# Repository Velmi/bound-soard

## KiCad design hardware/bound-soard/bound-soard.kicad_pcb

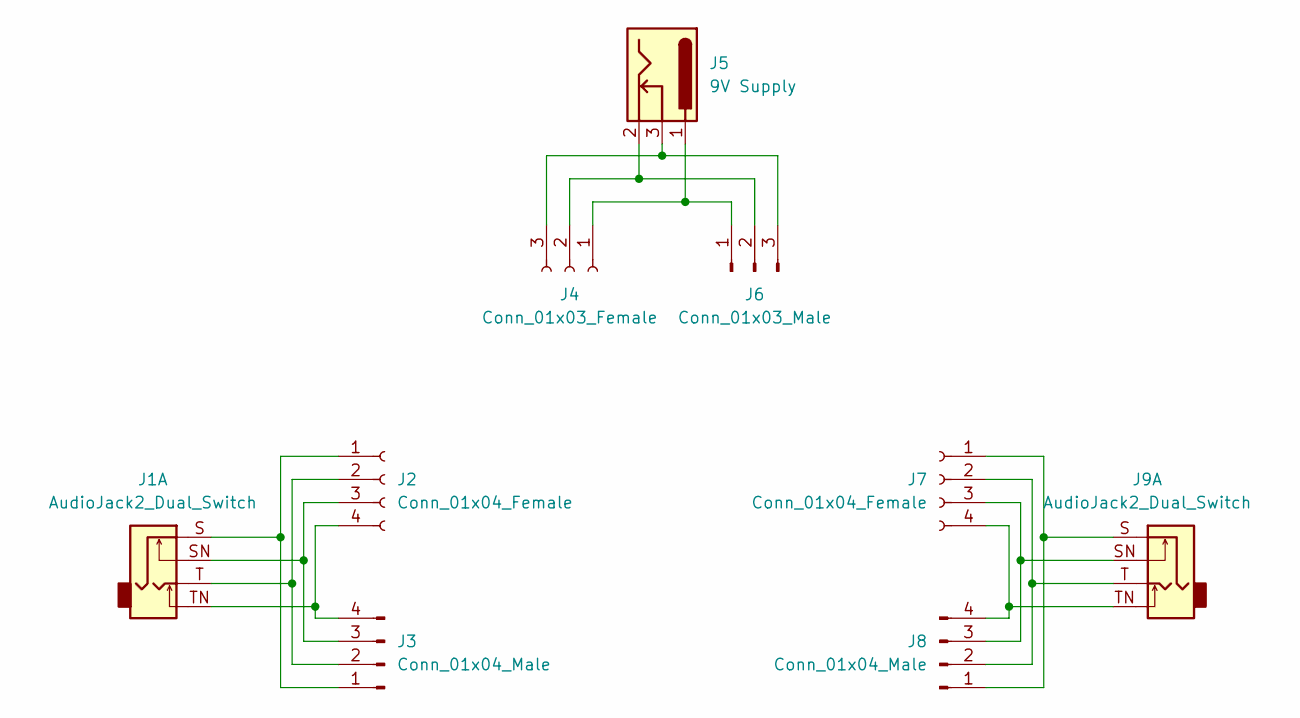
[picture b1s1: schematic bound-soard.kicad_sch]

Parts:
J1, J9: AudioJack2_Dual_Switch; Jack_6.35mm_Neutrik_NRJ4HF_Horizontal
J2, J7: Conn_01x04_Female; PinSocket_1x04_P2.54mm_Vertical
J3, J8: Conn_01x04_Male; PinHeader_1x04_P2.54mm_Vertical
J4: Conn_01x03_Female; PinSocket_1x03_P2.54mm_Vertical
J5: 9V Supply; BarrelJack_Horizontal
J6: Conn_01x03_Male; PinHeader_1x03_P2.54mm_Vertical

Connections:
unnamed: J1.S, J2.1, J3.1
unnamed: J1.SN, J2.3, J3.3
unnamed: J1.T, J2.2, J3.2
unnamed: J1.TN, J2.4, J3.4
unnamed: J4.1, J5.1, J6.1
unnamed: J4.2, J5.2, J6.2
unnamed: J4.3, J5.3, J6.3
unnamed: J7.1, J8.1, J9.S
unnamed: J7.2, J8.2, J9.T
unnamed: J7.3, J8.3, J9.SN
unnamed: J7.4, J8.4, J9.TN

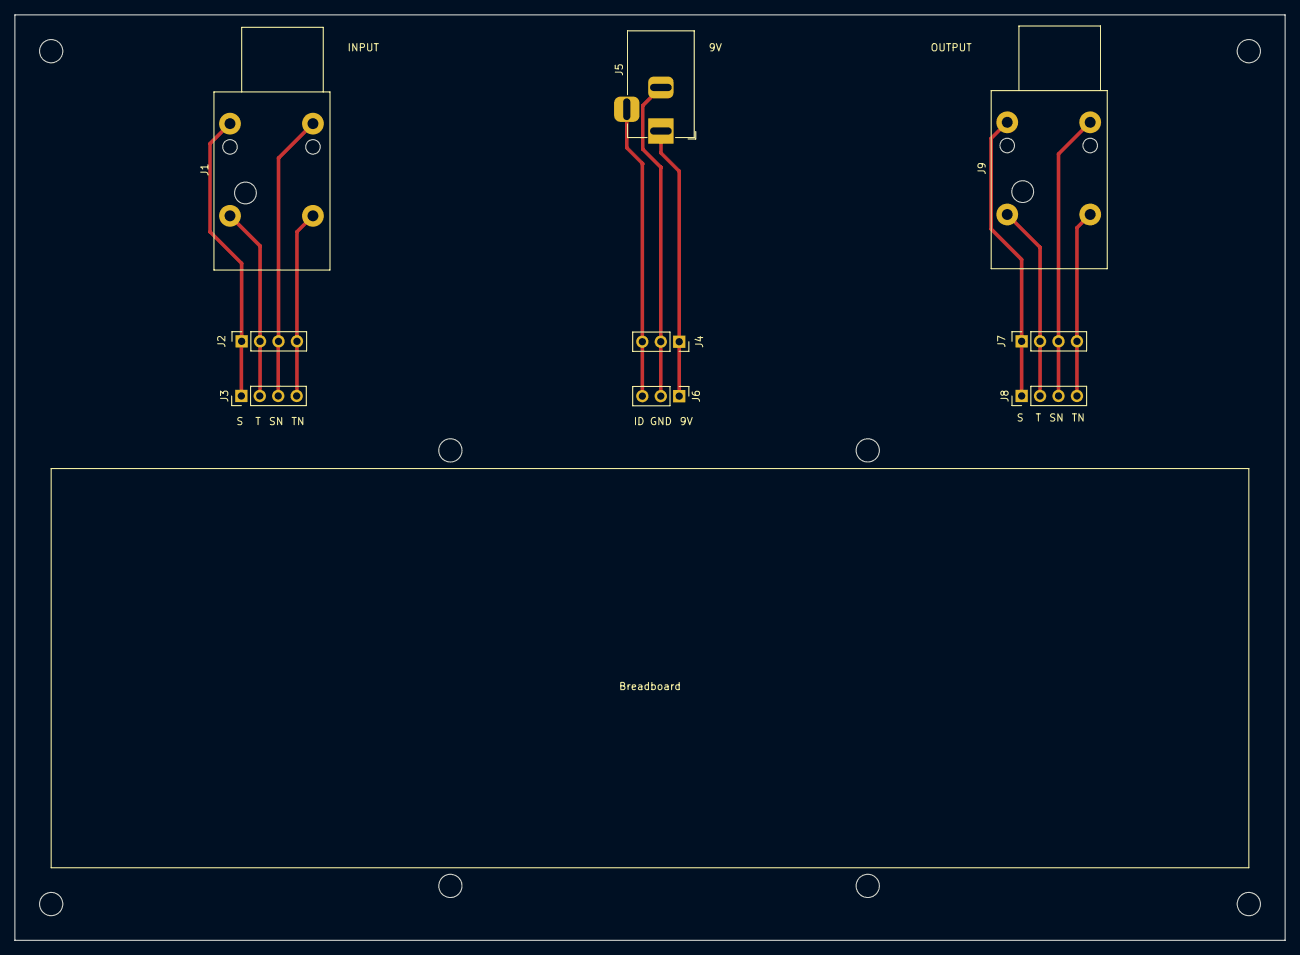
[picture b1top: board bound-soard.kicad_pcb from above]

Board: 2 copper layers, 175.0 x 127.5 mm, 9 parts (0 on the bottom side), 11 nets.

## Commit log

2022-08-30 added shematic, jack has to bee changed to 6.3mm
2022-09-01 probably final
2022-09-05 final
